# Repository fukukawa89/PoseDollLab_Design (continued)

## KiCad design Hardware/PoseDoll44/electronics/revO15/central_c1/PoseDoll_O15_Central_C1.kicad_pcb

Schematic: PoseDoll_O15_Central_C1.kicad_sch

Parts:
C1, C2: 10u X7R 10V; C_0603_1608Metric
C100, C102, C103, C104, C105, C200, C202, C203, C204, C205, C300, C302, C303, C304, C305, C400, C402, C403, C404, C405, C500, C502, C503, C504, C505, C600, C602, C603, C604, C605: 100n X7R 10V; C_0603_1608Metric
C101, C201, C301, C401, C501, C601: 1u X7R 10V; C_0603_1608Metric
D1: SS14 / 1A 40V; D_SMA
J1: CHAIN1 GND,3V3,SCK,MOSI,MISO,CS; JST_GH_SM06B-GHS-TB_1x06-1MP_P1.25mm_Horizontal
J2: CHAIN2 GND,3V3,SCK,MOSI,MISO,CS; JST_GH_SM06B-GHS-TB_1x06-1MP_P1.25mm_Horizontal
J3: CHAIN3 GND,3V3,SCK,MOSI,MISO,CS; JST_GH_SM06B-GHS-TB_1x06-1MP_P1.25mm_Horizontal
J4: CHAIN4 GND,3V3,SCK,MOSI,MISO,CS; JST_GH_SM06B-GHS-TB_1x06-1MP_P1.25mm_Horizontal
J5: CHAIN5 GND,3V3,SCK,MOSI,MISO,CS; JST_GH_SM06B-GHS-TB_1x06-1MP_P1.25mm_Horizontal
J6: CHAIN6 GND,3V3,SCK,MOSI,MISO,CS; JST_GH_SM06B-GHS-TB_1x06-1MP_P1.25mm_Horizontal
J7: 5V INPUT ONLY / JST PH 2; JST_PH_B2B-PH-SM4-TB_1x02-1MP_P2.00mm_Vertical
J8: Pololu D24V22F3 harness: GND, VIN5, VOUT3V3; JST_PH_B3B-PH-SM4-TB_1x03-1MP_P2.00mm_Vertical
Q1, Q2, Q3, Q4, Q5, Q6: 2N7002; SOT-23
R1, R2, R106, R206, R306, R406, R506, R606: 100k; R_0603_1608Metric
R100, R200, R300, R400, R500, R600: 88.7k 1%; R_0603_1608Metric
R101, R108, R109, R110, R201, R208, R209, R210, R301, R308, R309, R310, R401, R408, R409, R410, R501, R508, R509, R510, R601, R608, R609, R610: 47k; R_0603_1608Metric
R102, R107, R202, R207, R302, R307, R402, R407, R502, R507, R602, R607: 10k; R_0603_1608Metric
R103, R104, R105, R203, R204, R205, R303, R304, R305, R403, R404, R405, R503, R504, R505, R603, R604, R605: 100R; R_0603_1608Metric
TP1: P1_FAULT_N; TestPoint_Pad_D1.0mm
TP2: P2_FAULT_N; TestPoint_Pad_D1.0mm
TP3: P3_FAULT_N; TestPoint_Pad_D1.0mm
TP4: P4_FAULT_N; TestPoint_Pad_D1.0mm
TP5: P5_FAULT_N; TestPoint_Pad_D1.0mm
TP6: P6_FAULT_N; TestPoint_Pad_D1.0mm
U1: Seeed XIAO ESP32S3; 2x 1x7 P2.54 male pin strips; XIAO_ESP32S3_2x7_PTH
U100, U200, U300, U400, U500, U600: TPS2553DBVR-1 / latched-off; SOT-23-6
U101, U102, U103, U104, U201, U202, U203, U204, U301, U302, U303, U304, U401, U402, U403, U404, U501, U502, U503, U504, U601, U602, U603, U604: SN74LVC1G125DBVR; SOT-23-5

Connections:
/CS1: R102.2, U1.2 (D1_GPIO2), U103.2 (A), U104.1 (OE_N)
/CS2: R202.2, U1.4 (D3_GPIO4), U203.2 (A), U204.1 (OE_N)
/CS3: R302.2, U1.5 (D4_GPIO5), U303.2 (A), U304.1 (OE_N)
/CS4: R402.2, U1.6 (D5_GPIO6), U403.2 (A), U404.1 (OE_N)
/CS5: R502.2, U1.7 (D6_GPIO43), U503.2 (A), U504.1 (OE_N)
/CS6: R602.2, U1.8 (D7_GPIO44), U603.2 (A), U604.1 (OE_N)
/GND: C1.2, C2.2, C100.2, C101.2, C102.2, C103.2, C104.2, C105.2, C200.2, C201.2, C202.2, C203.2, C204.2, C205.2, C300.2, C301.2, C302.2, C303.2, C304.2, C305.2, C400.2, C401.2, C402.2, C403.2, C404.2, C405.2, C500.2, C501.2, C502.2, C503.2, C504.2, C505.2, C600.2, C601.2, C602.2, C603.2, C604.2, C605.2, J1.1, J2.1, J3.1, J4.1, J5.1, J6.1, J7.2, J8.1, Q1.2 (S), Q2.2 (S), Q3.2 (S), Q4.2 (S), Q5.2 (S), Q6.2 (S), R1.2, R100.2, R106.2, R108.2, R109.2, R200.2, R206.2, R208.2, R209.2, R300.2, R306.2, R308.2, R309.2, R400.2, R406.2, R408.2, R409.2, R500.2, R506.2, R508.2, R509.2, R600.2, R606.2, R608.2, R609.2, U1.13 (GND), U100.2 (GND), U101.3 (GND), U102.3 (GND), U103.3 (GND), U104.3 (GND), U200.2 (GND), U201.3 (GND), U202.3 (GND), U203.3 (GND), U204.3 (GND), U300.2 (GND), U301.3 (GND), U302.3 (GND), U303.3 (GND), U304.3 (GND), U400.2 (GND), U401.3 (GND), U402.3 (GND), U403.3 (GND), U404.3 (GND), U500.2 (GND), U501.3 (GND), U502.3 (GND), U503.3 (GND), U504.3 (GND), U600.2 (GND), U601.3 (GND), U602.3 (GND), U603.3 (GND), U604.3 (GND)
/IO_ENABLE: Q1.1 (G), Q2.1 (G), Q3.1 (G), Q4.1 (G), Q5.1 (G), Q6.1 (G), R1.1, U1.1 (D0_GPIO1)
/MCU_3V3: C103.1, C203.1, C303.1, C403.1, C503.1, C603.1, R2.2, R102.1, R202.1, R302.1, R402.1, R502.1, R602.1, U1.12 (3V3_MCU), U104.5 (VCC), U204.5 (VCC), U304.5 (VCC), U404.5 (VCC), U504.5 (VCC), U604.5 (VCC)
/MCU_5V: D1.1 (K), U1.14 (5V_VBUS)
/MISO: R2.1, U1.10 (D9_GPIO8), U104.4 (Y), U204.4 (Y), U304.4 (Y), U404.4 (Y), U504.4 (Y), U604.4 (Y)
/MOSI: U1.11 (D10_GPIO9), U102.2 (A), U202.2 (A), U302.2 (A), U402.2 (A), U502.2 (A), U602.2 (A)
/P1_3V3: C101.1, C102.1, C104.1, C105.1, J1.2, R101.1, R107.1, U100.6 (OUT), U101.5 (VCC), U102.5 (VCC), U103.5 (VCC)
/P1_CS: J1.6, R105.2, R107.2
/P1_CS_DRV: R105.1, U103.4 (Y)
/P1_FAULT_N: R110.2, TP1.1, U100.4 (FAULT_N)
/P1_ILIM: R100.1, U100.5 (ILIM)
/P1_MISO: J1.5, R106.1, U104.2 (A)
/P1_MOSI: J1.4, R104.2, R109.1
/P1_MOSI_DRV: R104.1, U102.4 (Y)
/P1_OE_N: Q1.3 (D), R101.2, U101.1 (OE_N), U102.1 (OE_N), U103.1 (OE_N)
/P1_SCK: J1.3, R103.2, R108.1
/P1_SCK_DRV: R103.1, U101.4 (Y)
/P2_3V3: C201.1, C202.1, C204.1, C205.1, J2.2, R201.1, R207.1, U200.6 (OUT), U201.5 (VCC), U202.5 (VCC), U203.5 (VCC)
/P2_CS: J2.6, R205.2, R207.2
/P2_CS_DRV: R205.1, U203.4 (Y)
/P2_FAULT_N: R210.2, TP2.1, U200.4 (FAULT_N)
/P2_ILIM: R200.1, U200.5 (ILIM)
/P2_MISO: J2.5, R206.1, U204.2 (A)
/P2_MOSI: J2.4, R204.2, R209.1
/P2_MOSI_DRV: R204.1, U202.4 (Y)
/P2_OE_N: Q2.3 (D), R201.2, U201.1 (OE_N), U202.1 (OE_N), U203.1 (OE_N)
/P2_SCK: J2.3, R203.2, R208.1
/P2_SCK_DRV: R203.1, U201.4 (Y)
/P3_3V3: C301.1, C302.1, C304.1, C305.1, J3.2, R301.1, R307.1, U300.6 (OUT), U301.5 (VCC), U302.5 (VCC), U303.5 (VCC)
/P3_CS: J3.6, R305.2, R307.2
/P3_CS_DRV: R305.1, U303.4 (Y)
/P3_FAULT_N: R310.2, TP3.1, U300.4 (FAULT_N)
/P3_ILIM: R300.1, U300.5 (ILIM)
/P3_MISO: J3.5, R306.1, U304.2 (A)
/P3_MOSI: J3.4, R304.2, R309.1
/P3_MOSI_DRV: R304.1, U302.4 (Y)
/P3_OE_N: Q3.3 (D), R301.2, U301.1 (OE_N), U302.1 (OE_N), U303.1 (OE_N)
/P3_SCK: J3.3, R303.2, R308.1
/P3_SCK_DRV: R303.1, U301.4 (Y)
/P4_3V3: C401.1, C402.1, C404.1, C405.1, J4.2, R401.1, R407.1, U400.6 (OUT), U401.5 (VCC), U402.5 (VCC), U403.5 (VCC)
/P4_CS: J4.6, R405.2, R407.2
/P4_CS_DRV: R405.1, U403.4 (Y)
/P4_FAULT_N: R410.2, TP4.1, U400.4 (FAULT_N)
/P4_ILIM: R400.1, U400.5 (ILIM)
/P4_MISO: J4.5, R406.1, U404.2 (A)
/P4_MOSI: J4.4, R404.2, R409.1
/P4_MOSI_DRV: R404.1, U402.4 (Y)
/P4_OE_N: Q4.3 (D), R401.2, U401.1 (OE_N), U402.1 (OE_N), U403.1 (OE_N)
/P4_SCK: J4.3, R403.2, R408.1
/P4_SCK_DRV: R403.1, U401.4 (Y)
/P5_3V3: C501.1, C502.1, C504.1, C505.1, J5.2, R501.1, R507.1, U500.6 (OUT), U501.5 (VCC), U502.5 (VCC), U503.5 (VCC)
/P5_CS: J5.6, R505.2, R507.2
/P5_CS_DRV: R505.1, U503.4 (Y)
/P5_FAULT_N: R510.2, TP5.1, U500.4 (FAULT_N)
/P5_ILIM: R500.1, U500.5 (ILIM)
/P5_MISO: J5.5, R506.1, U504.2 (A)
/P5_MOSI: J5.4, R504.2, R509.1
/P5_MOSI_DRV: R504.1, U502.4 (Y)
/P5_OE_N: Q5.3 (D), R501.2, U501.1 (OE_N), U502.1 (OE_N), U503.1 (OE_N)
/P5_SCK: J5.3, R503.2, R508.1
/P5_SCK_DRV: R503.1, U501.4 (Y)
/P6_3V3: C601.1, C602.1, C604.1, C605.1, J6.2, R601.1, R607.1, U600.6 (OUT), U601.5 (VCC), U602.5 (VCC), U603.5 (VCC)
/P6_CS: J6.6, R605.2, R607.2
/P6_CS_DRV: R605.1, U603.4 (Y)
/P6_FAULT_N: R610.2, TP6.1, U600.4 (FAULT_N)
/P6_ILIM: R600.1, U600.5 (ILIM)
/P6_MISO: J6.5, R606.1, U604.2 (A)
/P6_MOSI: J6.4, R604.2, R609.1
/P6_MOSI_DRV: R604.1, U602.4 (Y)
/P6_OE_N: Q6.3 (D), R601.2, U601.1 (OE_N), U602.1 (OE_N), U603.1 (OE_N)
/P6_SCK: J6.3, R603.2, R608.1
/P6_SCK_DRV: R603.1, U601.4 (Y)
/SCK: U1.9 (D8_GPIO7), U101.2 (A), U201.2 (A), U301.2 (A), U401.2 (A), U501.2 (A), U601.2 (A)
/SENSOR_3V3: C2.1, C100.1, C200.1, C300.1, C400.1, C500.1, C600.1, J8.3, R110.1, R210.1, R310.1, R410.1, R510.1, R610.1, U100.1 (IN), U100.3 (EN), U200.1 (IN), U200.3 (EN), U300.1 (IN), U300.3 (EN), U400.1 (IN), U400.3 (EN), U500.1 (IN), U500.3 (EN), U600.1 (IN), U600.3 (EN)
/VIN_5V: C1.1, D1.2 (A), J7.1, J8.2

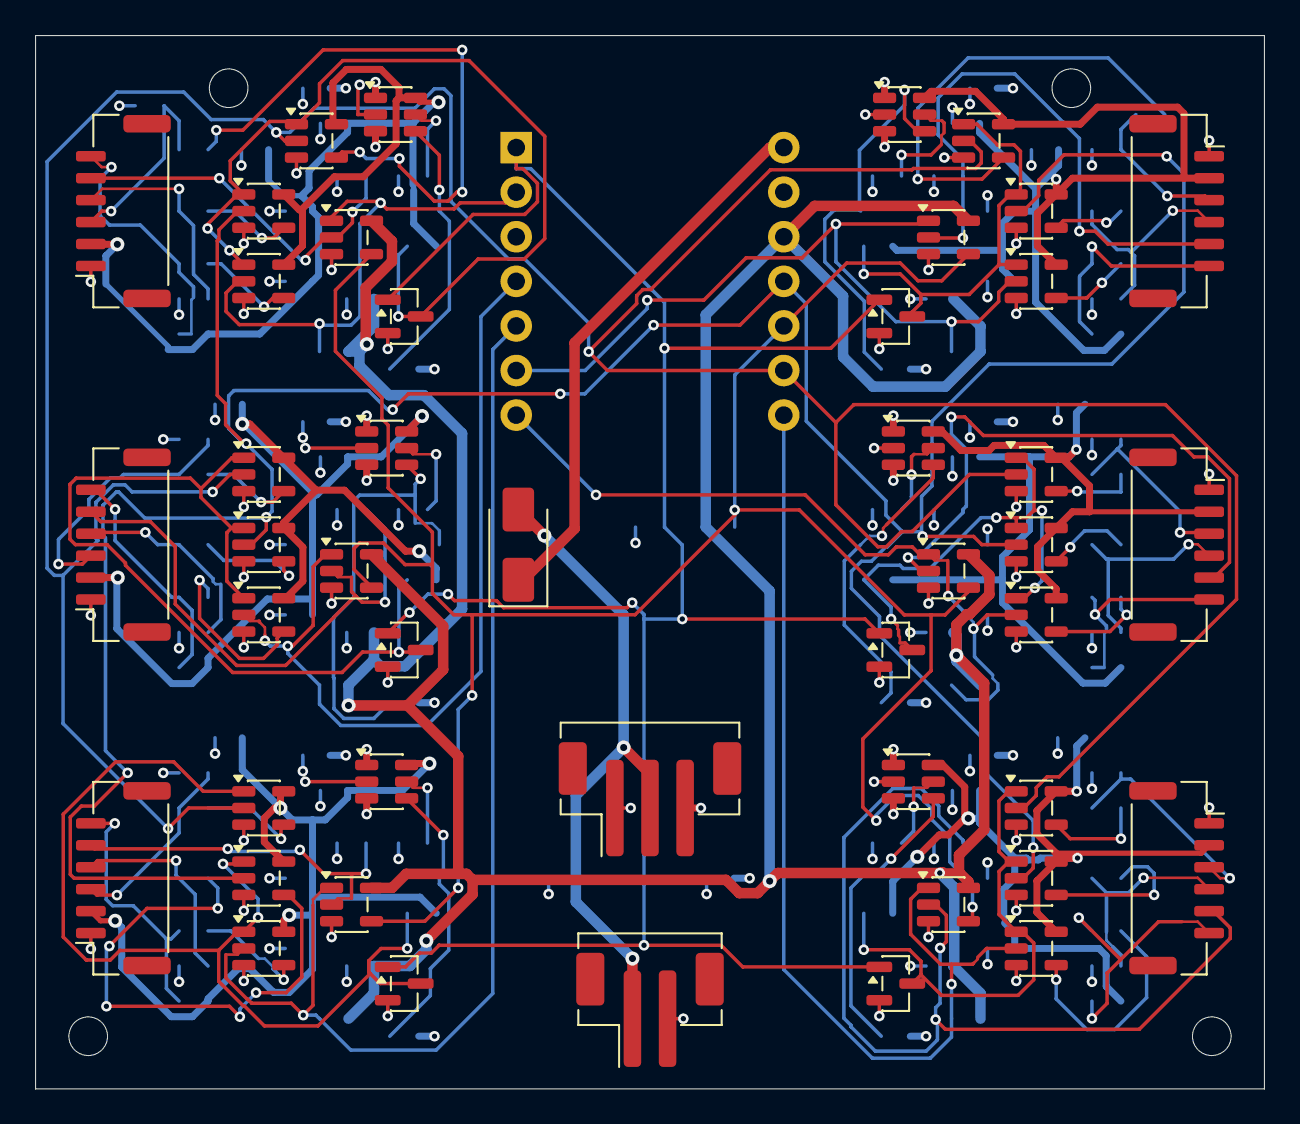
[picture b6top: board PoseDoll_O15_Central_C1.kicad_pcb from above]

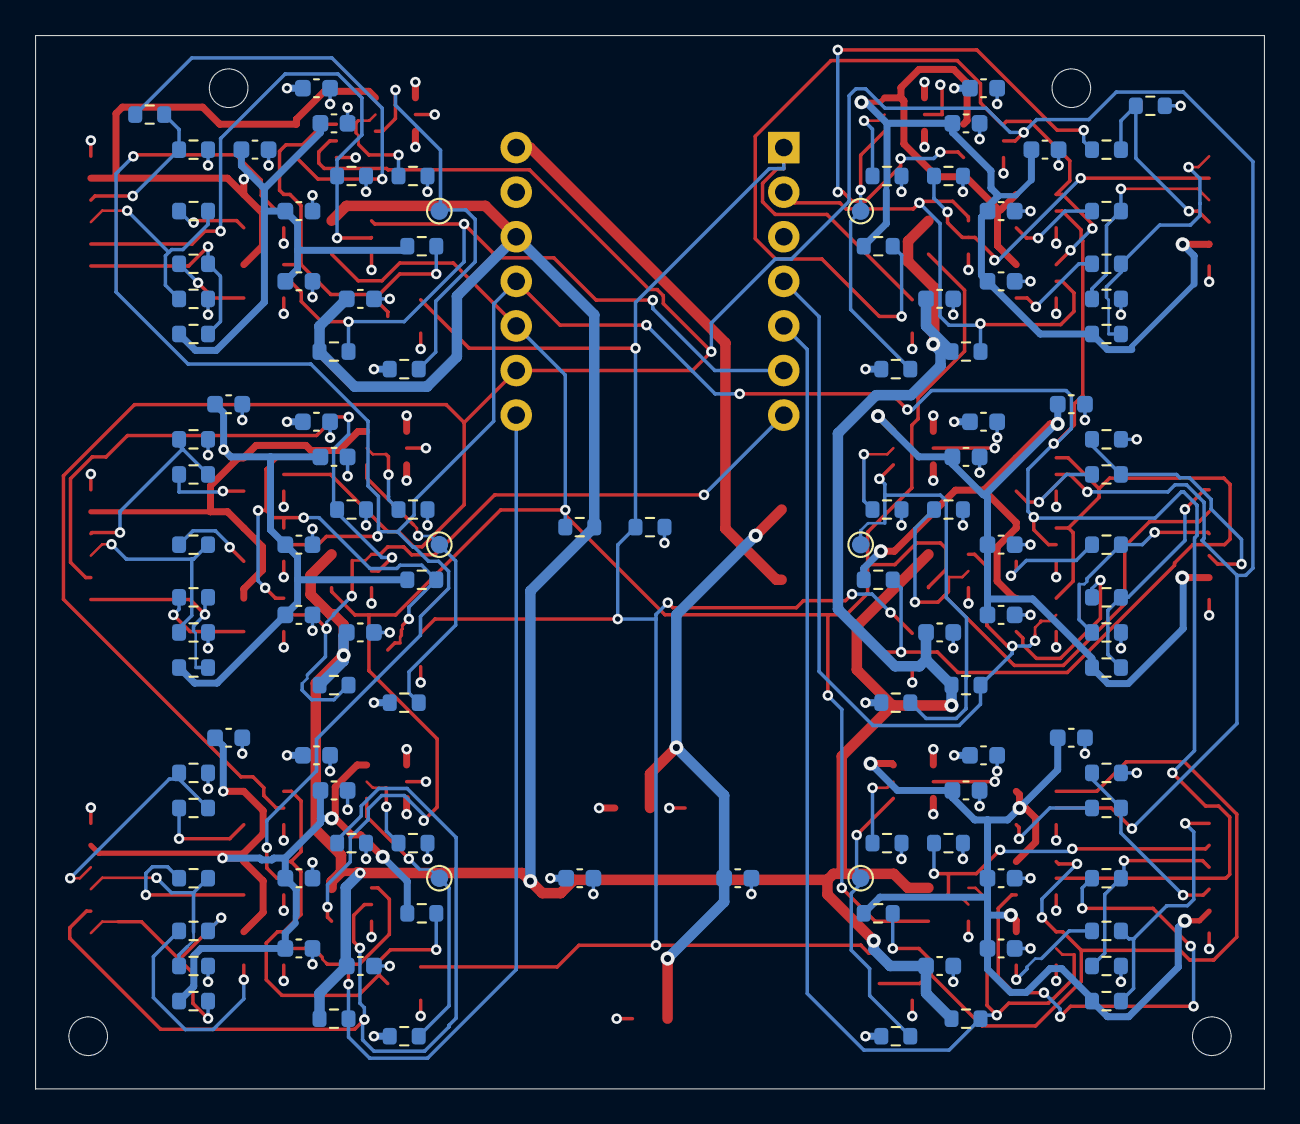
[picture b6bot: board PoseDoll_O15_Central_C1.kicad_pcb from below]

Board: 4 copper layers, 70.0 x 60.0 mm, 162 parts (112 on the bottom side), 81 nets.

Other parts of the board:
H1, H2, H3, H4: MountingHole_2.2mm_M2
